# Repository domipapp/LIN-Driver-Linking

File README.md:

# LIN meghajtó illesztése STK3700 mikrokontrollerhez és visszapillantó tükör vezérlése számítógépről
A project az 5. féléves Témalaboratóium kurzus keretein belül valósult meg. A konzulensem Scherer Balázs volt.
A projekt során meg kellett tervezni egy nyákot olyan kapcsolással amely illeszthető STM3700 mikrokontrollerhez, számítőgéptől kapott LIN üzenetek
megfelelő feszültségszintre konvertálását el tudja végezni és képes elegendő áramot szolgáltani a visszapillantó tükör vezérléséhez.
Az üzenetek dekódolását és a tükör irányítását a mikrokontroller végzi.

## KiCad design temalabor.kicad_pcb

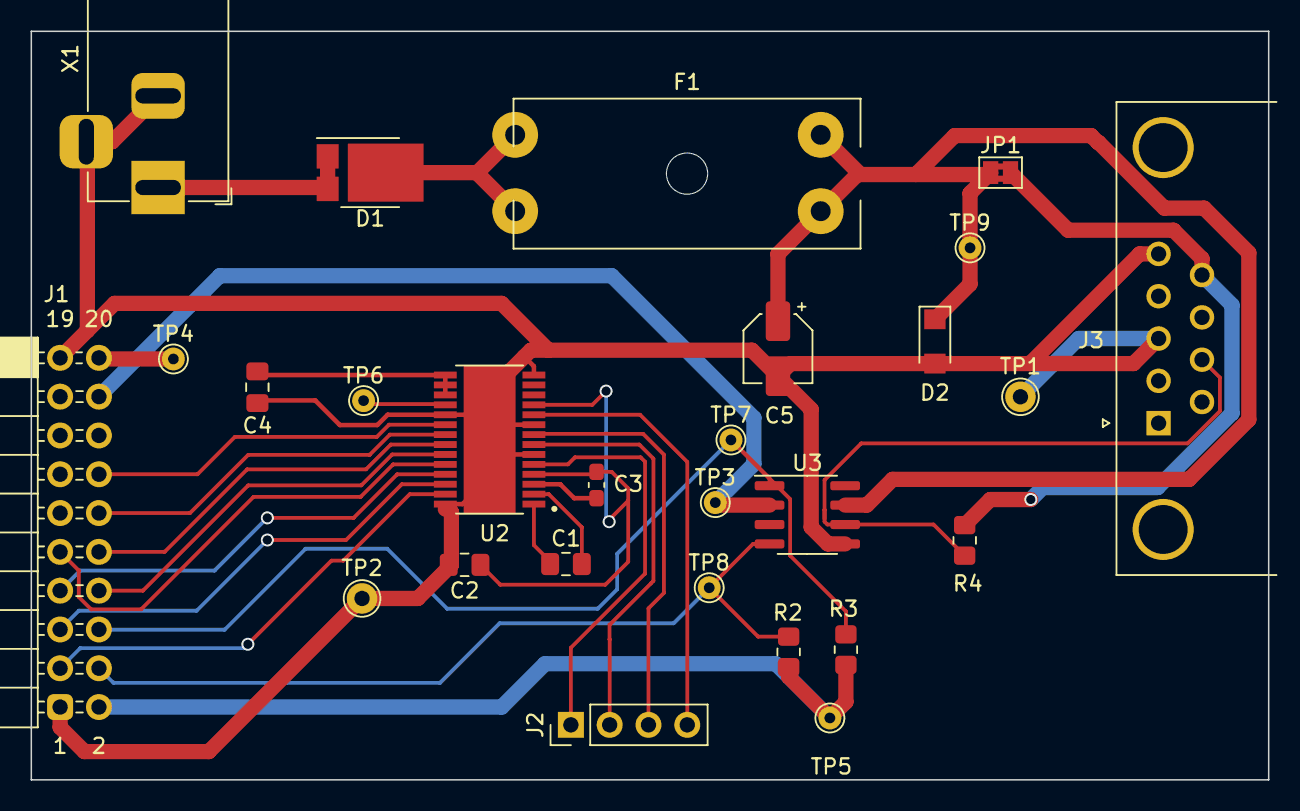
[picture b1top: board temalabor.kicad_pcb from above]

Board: 2 copper layers, 81.0 x 49.0 mm, 27 parts (0 on the bottom side), 29 nets.

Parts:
C1: 0.1u; C_0805_2012Metric_Pad1.18x1.45mm_HandSolder
C2: 10u; C_0805_2012Metric_Pad1.18x1.45mm_HandSolder
C3: 0.1u; C_0603_1608Metric_Pad1.08x0.95mm_HandSolder
C4: 0.47u; C_0805_2012Metric_Pad1.18x1.45mm_HandSolder
C5: 100u; CP_Elec_4x3.9
D1: PMEG045T150EIPD; Nexperia_CFP15_SOT-1289
D2: BZD27Cxx; D_SMF
F1: Fuse; Fuseholder_Cylinder-5x20mm_Schurter_0031_8201_Horizontal_Op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
J1: STK3700_Exp_Conn; PinSocket_2x10_P2.54mm_Horizontal_Reversed
J2: Conn_01x04_Male; PinHeader_1x04_P2.54mm_Vertical
J3: DB9_Female; DSUB-9_Male_Horizontal_P2.77x2.84mm_EdgePinOffset4.94mm_Hou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
JP1: Jumper_2_Open; SolderJumper-2_P1.3mm_Bridged2Bar_Pad1.0x1.5mm
R2, R3: 10k; R_0805_2012Metric_Pad1.20x1.40mm_HandSolder
R4: 1k; R_0805_2012Metric_Pad1.20x1.40mm_HandSolder
TP1, TP2: GND; TestPoint_THTPad_D2.0mm_Drill1.0mm
TP3: 5V; TestPoint_THTPad_D1.5mm_Drill0.7mm
TP4: 3V3; TestPoint_THTPad_D1.5mm_Drill0.7mm
TP5: VMCU; TestPoint_THTPad_D1.5mm_Drill0.7mm
TP6: NFAULT; TestPoint_THTPad_D1.5mm_Drill0.7mm
TP7: Rx; TestPoint_THTPad_D1.5mm_Drill0.7mm
TP8: Tx; TestPoint_THTPad_D1.5mm_Drill0.7mm
TP9: 12V; TestPoint_THTPad_D1.5mm_Drill0.7mm
U2: DRV8844PWPR; IC_DRV8844PWPR
U3: TJA1029T; SOIC-8_3.9x4.9mm_P1.27mm
X1: FC681478; BarrelJack_Horizontal

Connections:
12v: J3.9, JP1.2 (B), R4.1
+3V3: J1.20 (3V3), TP4.1
+5V: J1.18 (5V), TP3.1, U3.2 (~SLP)
CP1: C1.1, U2.1 (CP1)
CP2: C1.2, U2.2 (CP2)
EN1: J1.5 (PC3), U2.26 (EN1)
EN2: J1.9 (PC5), U2.24 (EN2)
EN3: J1.10 (PD3), U2.22 (EN3)
EN4: J1.14 (PD5), U2.20 (EN4)
GND: C2.2, C4.2, C5.2, D2.2 (A), J1.1 (GND), J1.19 (GND), J3.3, J3.5, TP1.1, TP2.1, U2.6 (SRC12), U2.9 (SRC34), U2.14 (VNEG_14), U2.19 (LGND), U2.28 (VNEG_28), U2.29 (VNEG_29), U3.5 (GND), X1.2, X1.3
IN1: J1.3 (PC0), U2.27 (IN1)
IN2: J1.7 (PC4), U2.25 (IN2)
IN3: J1.8 (PD2), U2.23 (IN3)
IN4: J1.12 (PD4), U2.21 (IN4)
unnamed: C2.1, C3.1, U2.4 (VM_4), U2.11 (VM_11)
unnamed: C5.1, D2.1 (K), F1.2, JP1.1 (A), TP9.1, U3.7 (VBAT)
unnamed: D1.1 (A), D1.2 (A), X1.1
unnamed: D1.3 (K), F1.1
unnamed: J2.1, U2.5 (OUT1)
unnamed: J2.2, U2.7 (OUT2)
unnamed: J2.3, U2.8 (OUT3)
unnamed: J2.4, U2.10 (OUT4)
unnamed: J3.7, R4.2, U3.6 (LIN)
unnamed: TP6.1, U2.18 (NFAULT)
Rx: J1.6 (PD1), R3.2, TP7.1, U3.1 (RXD)
Tx: J1.4 (PD0), R2.2, TP8.1, U3.4 (TXD)
V3P3OUT: C4.1, U2.15 (V3P3OUT), U2.16 (NRESET), U2.17 (NSLEEP)
VCP: C3.2, U2.3 (VCP)
VMCU: J1.2 (VMCU), R2.1, R3.1, TP5.1

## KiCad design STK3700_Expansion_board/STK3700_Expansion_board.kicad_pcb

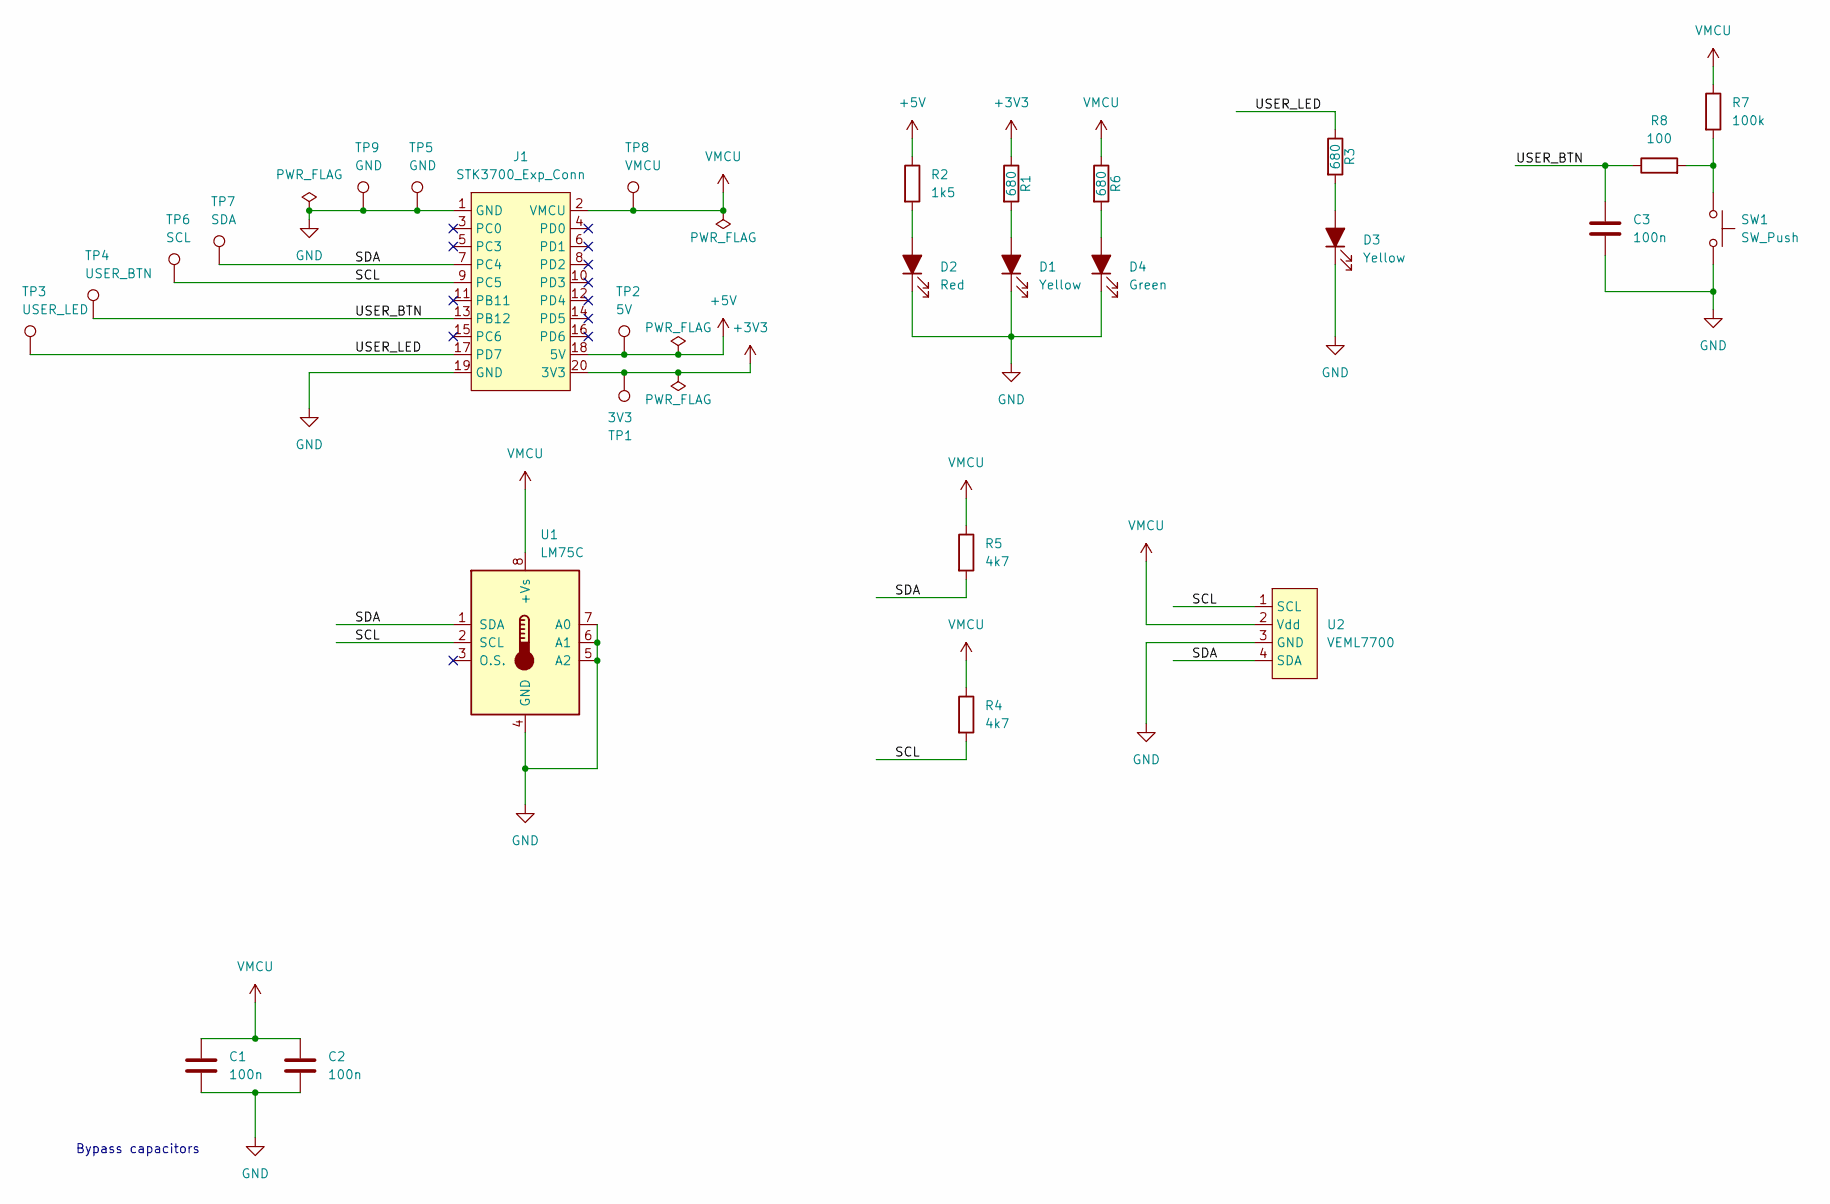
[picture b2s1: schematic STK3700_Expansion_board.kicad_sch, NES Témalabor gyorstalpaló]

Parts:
C1, C2, C3: 100n; C_0603_1608Metric_Pad1.08x0.95mm_HandSolder
D1, D3: Yellow; LED_0805_2012Metric_Pad1.15x1.40mm_HandSolder
D2: Red; LED_0805_2012Metric_Pad1.15x1.40mm_HandSolder
D4: Green; LED_0805_2012Metric_Pad1.15x1.40mm_HandSolder
J1: STK3700_Exp_Conn; PinSocket_2x10_P2.54mm_Horizontal_Reversed
R1, R3, R6: 680; R_0805_2012Metric_Pad1.20x1.40mm_HandSolder
R2: 1k5; R_0805_2012Metric_Pad1.20x1.40mm_HandSolder
R4, R5: 4k7; R_0805_2012Metric_Pad1.20x1.40mm_HandSolder
R7: 100k; R_0805_2012Metric_Pad1.20x1.40mm_HandSolder
R8: 100; R_0805_2012Metric_Pad1.20x1.40mm_HandSolder
SW1: SW_Push; SW_PUSH_6mm
TP1: 3V3; TestPoint_THTPad_D1.5mm_Drill0.7mm
TP2: 5V; TestPoint_THTPad_D1.5mm_Drill0.7mm
TP3: USER_LED; TestPoint_THTPad_D1.5mm_Drill0.7mm
TP4: USER_BTN; TestPoint_THTPad_D1.5mm_Drill0.7mm
TP5, TP9: GND; TestPoint_THTPad_D2.0mm_Drill1.0mm
TP6: SCL; TestPoint_THTPad_D1.5mm_Drill0.7mm
TP7: SDA; TestPoint_THTPad_D1.5mm_Drill0.7mm
TP8: VMCU; TestPoint_THTPad_D1.5mm_Drill0.7mm
U1: LM75C; SO-8_3.9x4.9mm_P1.27mm
U2: VEML7700; VEML7700_Top_View

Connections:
+3V3: J1.20 (3V3), R1.1, TP1.1
+5V: J1.18 (5V), R2.1, TP2.1
/SCL: J1.9 (PC5), R4.2, TP6.1, U1.2 (SCL), U2.1 (SCL)
/SDA: J1.7 (PC4), R5.2, TP7.1, U1.1 (SDA), U2.4 (SDA)
/USER_BTN: C3.1, J1.13 (PB12), R8.1, TP4.1
/USER_LED: J1.17 (PD7), R3.1, TP3.1
GND: C1.2, C2.2, C3.2, D1.1 (K), D2.1 (K), D3.1 (K), D4.1 (K), J1.1 (GND), J1.19 (GND), SW1.2, TP5.1, TP9.1, U1.4 (GND), U1.5 (A2), U1.6 (A1), U1.7 (A0), U2.3 (GND)
unnamed: D3.2 (A), R3.2
unnamed: D2.2 (A), R2.2
unnamed: D1.2 (A), R1.2
unnamed: D4.2 (A), R6.2
unnamed: R7.2, R8.2, SW1.1
VMCU: C1.1, C2.1, J1.2 (VMCU), R4.1, R5.1, R6.1, R7.1, TP8.1, U1.8 (+Vs), U2.2 (Vdd)

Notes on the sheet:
Bypass capacitors

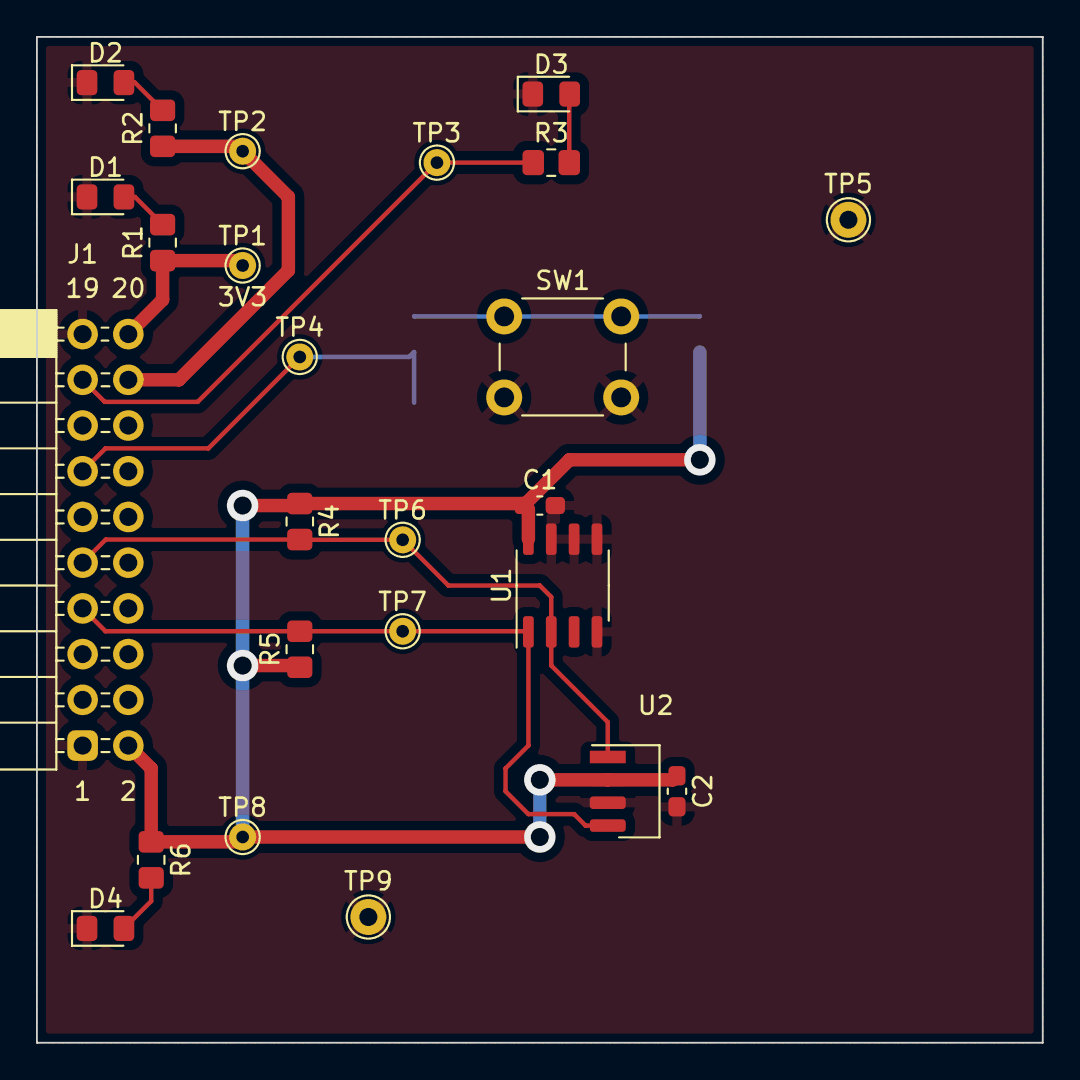
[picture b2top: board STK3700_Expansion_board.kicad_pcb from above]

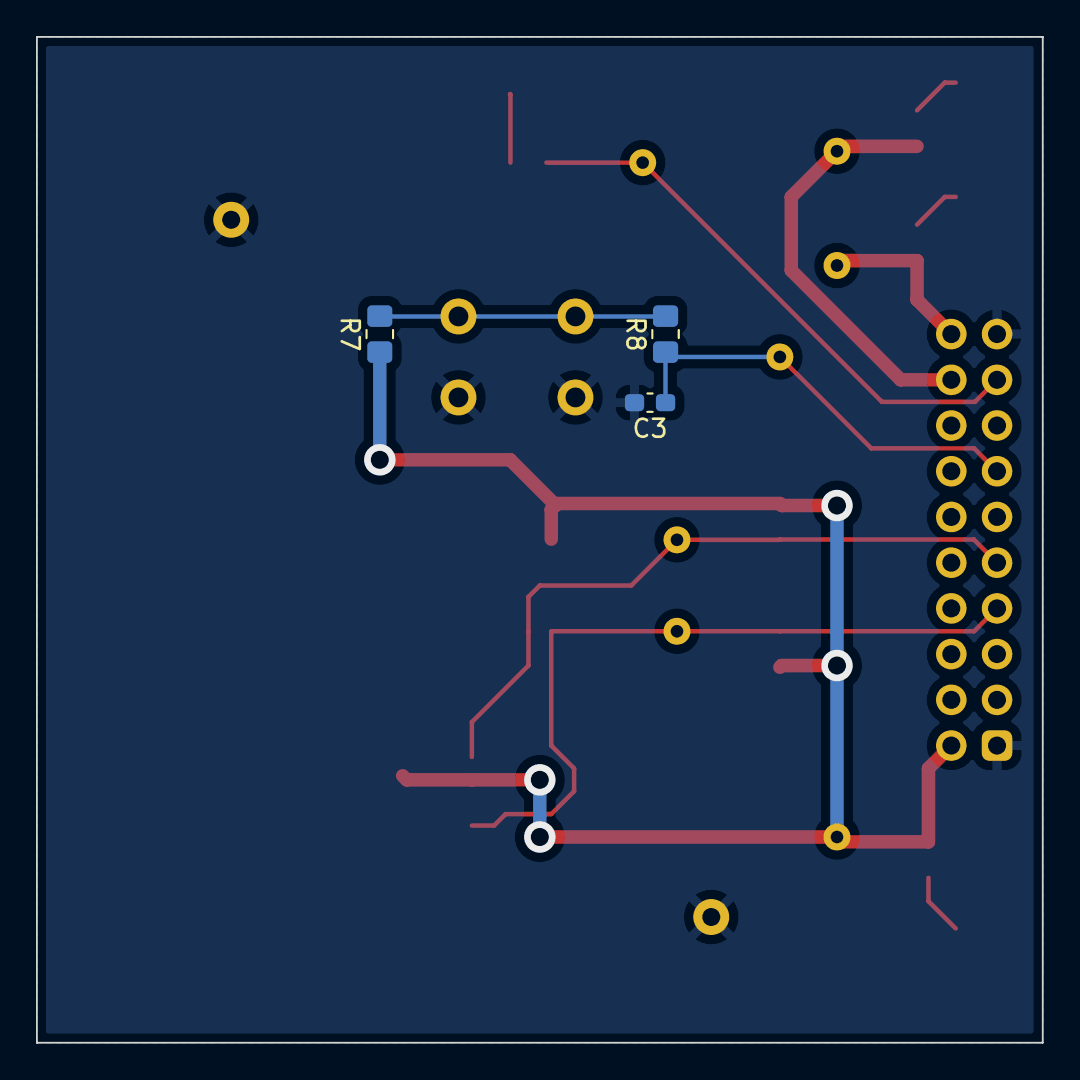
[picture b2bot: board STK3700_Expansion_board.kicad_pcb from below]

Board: 2 copper layers, 55.9 x 55.9 mm, 28 parts (3 on the bottom side), 13 nets.

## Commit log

2023-06-10 Refactoring
